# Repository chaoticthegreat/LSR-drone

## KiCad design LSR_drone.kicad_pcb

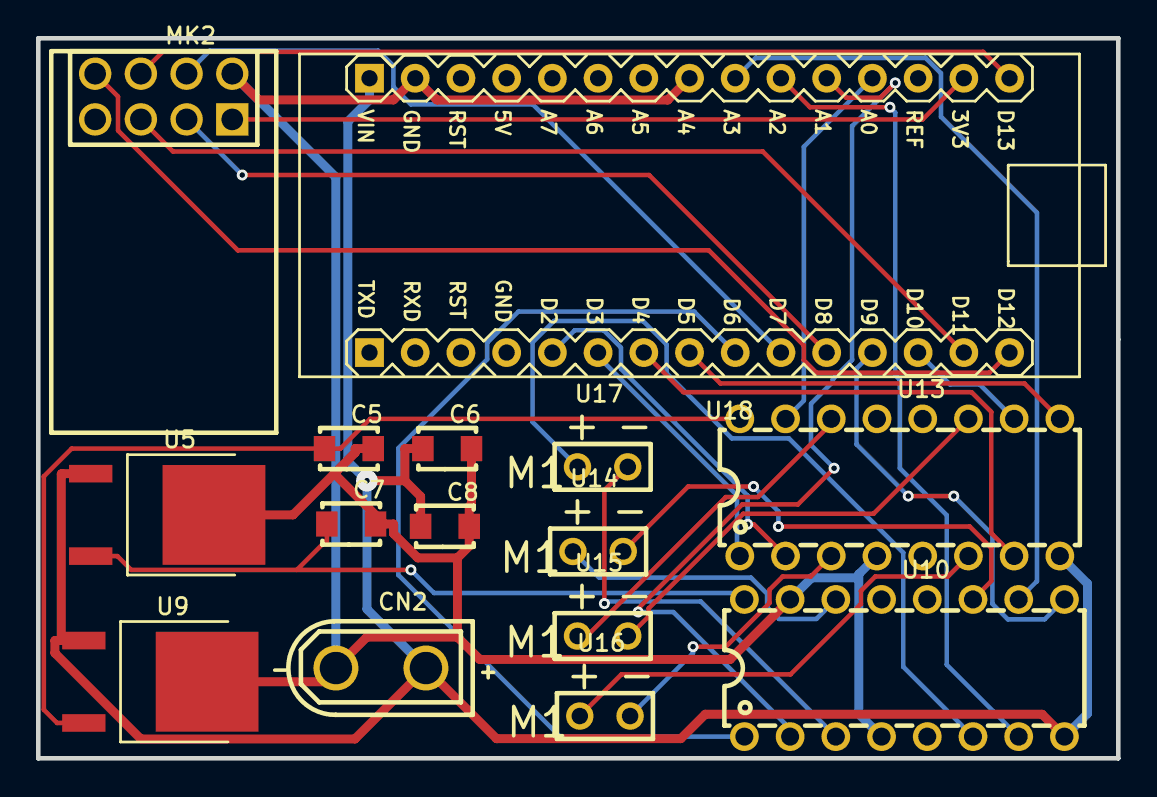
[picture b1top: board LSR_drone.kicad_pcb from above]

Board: 2 copper layers, 60.0 x 40.0 mm, 15 parts (0 on the bottom side), 29 nets.

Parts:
C5, C6, C7, C8: 330nF; CAP-SMD_L3.2-W1.6
CN2: XT30UPB-M; CONN-TH_XT30UPB-M
MK2: NRF24L01; WIRELM-SMD_NRF24L01
U5, U9: LM7805-5V; TO-252-2_L6.6-W6.1-P4.58-LS9.9-TL
U10, U13: L293D; DIP-16_L20.0-W6.4-P2.54-LS7.6-BL
U14, U15, U16, U17: DC Motor; TT DC MOTOR
U18: ARDUINO_NANO; COMM-TH_ARDUINO_NANO

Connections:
C5_1: C5.1, U9.3, U13.16
C7_1: C7.1, U5.3, U10.16
GND: C5.2, C6.2, C7.2, C8.2, CN2.1, MK2.2, U5.2, U9.2, U10.4, U10.15, U13.4, U18.23, U18.29
MK2_1: MK2.1, U18.17
MK2_3: MK2.3, U18.11
MK2_4: MK2.4, U18.10
MK2_5: MK2.5, U18.14
MK2_6: MK2.6, U18.16
MK2_8: MK2.8, U18.15
U10_1: U10.1, U18.9
U10_2: U10.2, U18.20
U10_3: U10.3, U17.2
U10_6: U10.6, U17.1
U10_7: U10.7, U18.21
U10_9: U10.9, U18.12
U10_10: U10.10, U18.22
U10_11: U10.11, U14.2
U10_14: U10.14, U14.1
U13_1: U13.1, U18.6
U13_2: U13.2, U18.5
U13_3: U13.3, U16.2
U13_6: U13.6, U16.1
U13_7: U13.7, U18.7
U13_9: U13.9, U18.8
U13_10: U13.10, U18.13
U13_11: U13.11, U15.2
U13_14: U13.14, U15.1
U13_15: U13.15, U18.19
VCC: C6.1, C8.1, CN2.2, U5.1, U9.1, U10.8, U13.8, U18.30

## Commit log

2024-08-10 init
2024-08-10 Create LICENSE
2024-08-10 stuff
